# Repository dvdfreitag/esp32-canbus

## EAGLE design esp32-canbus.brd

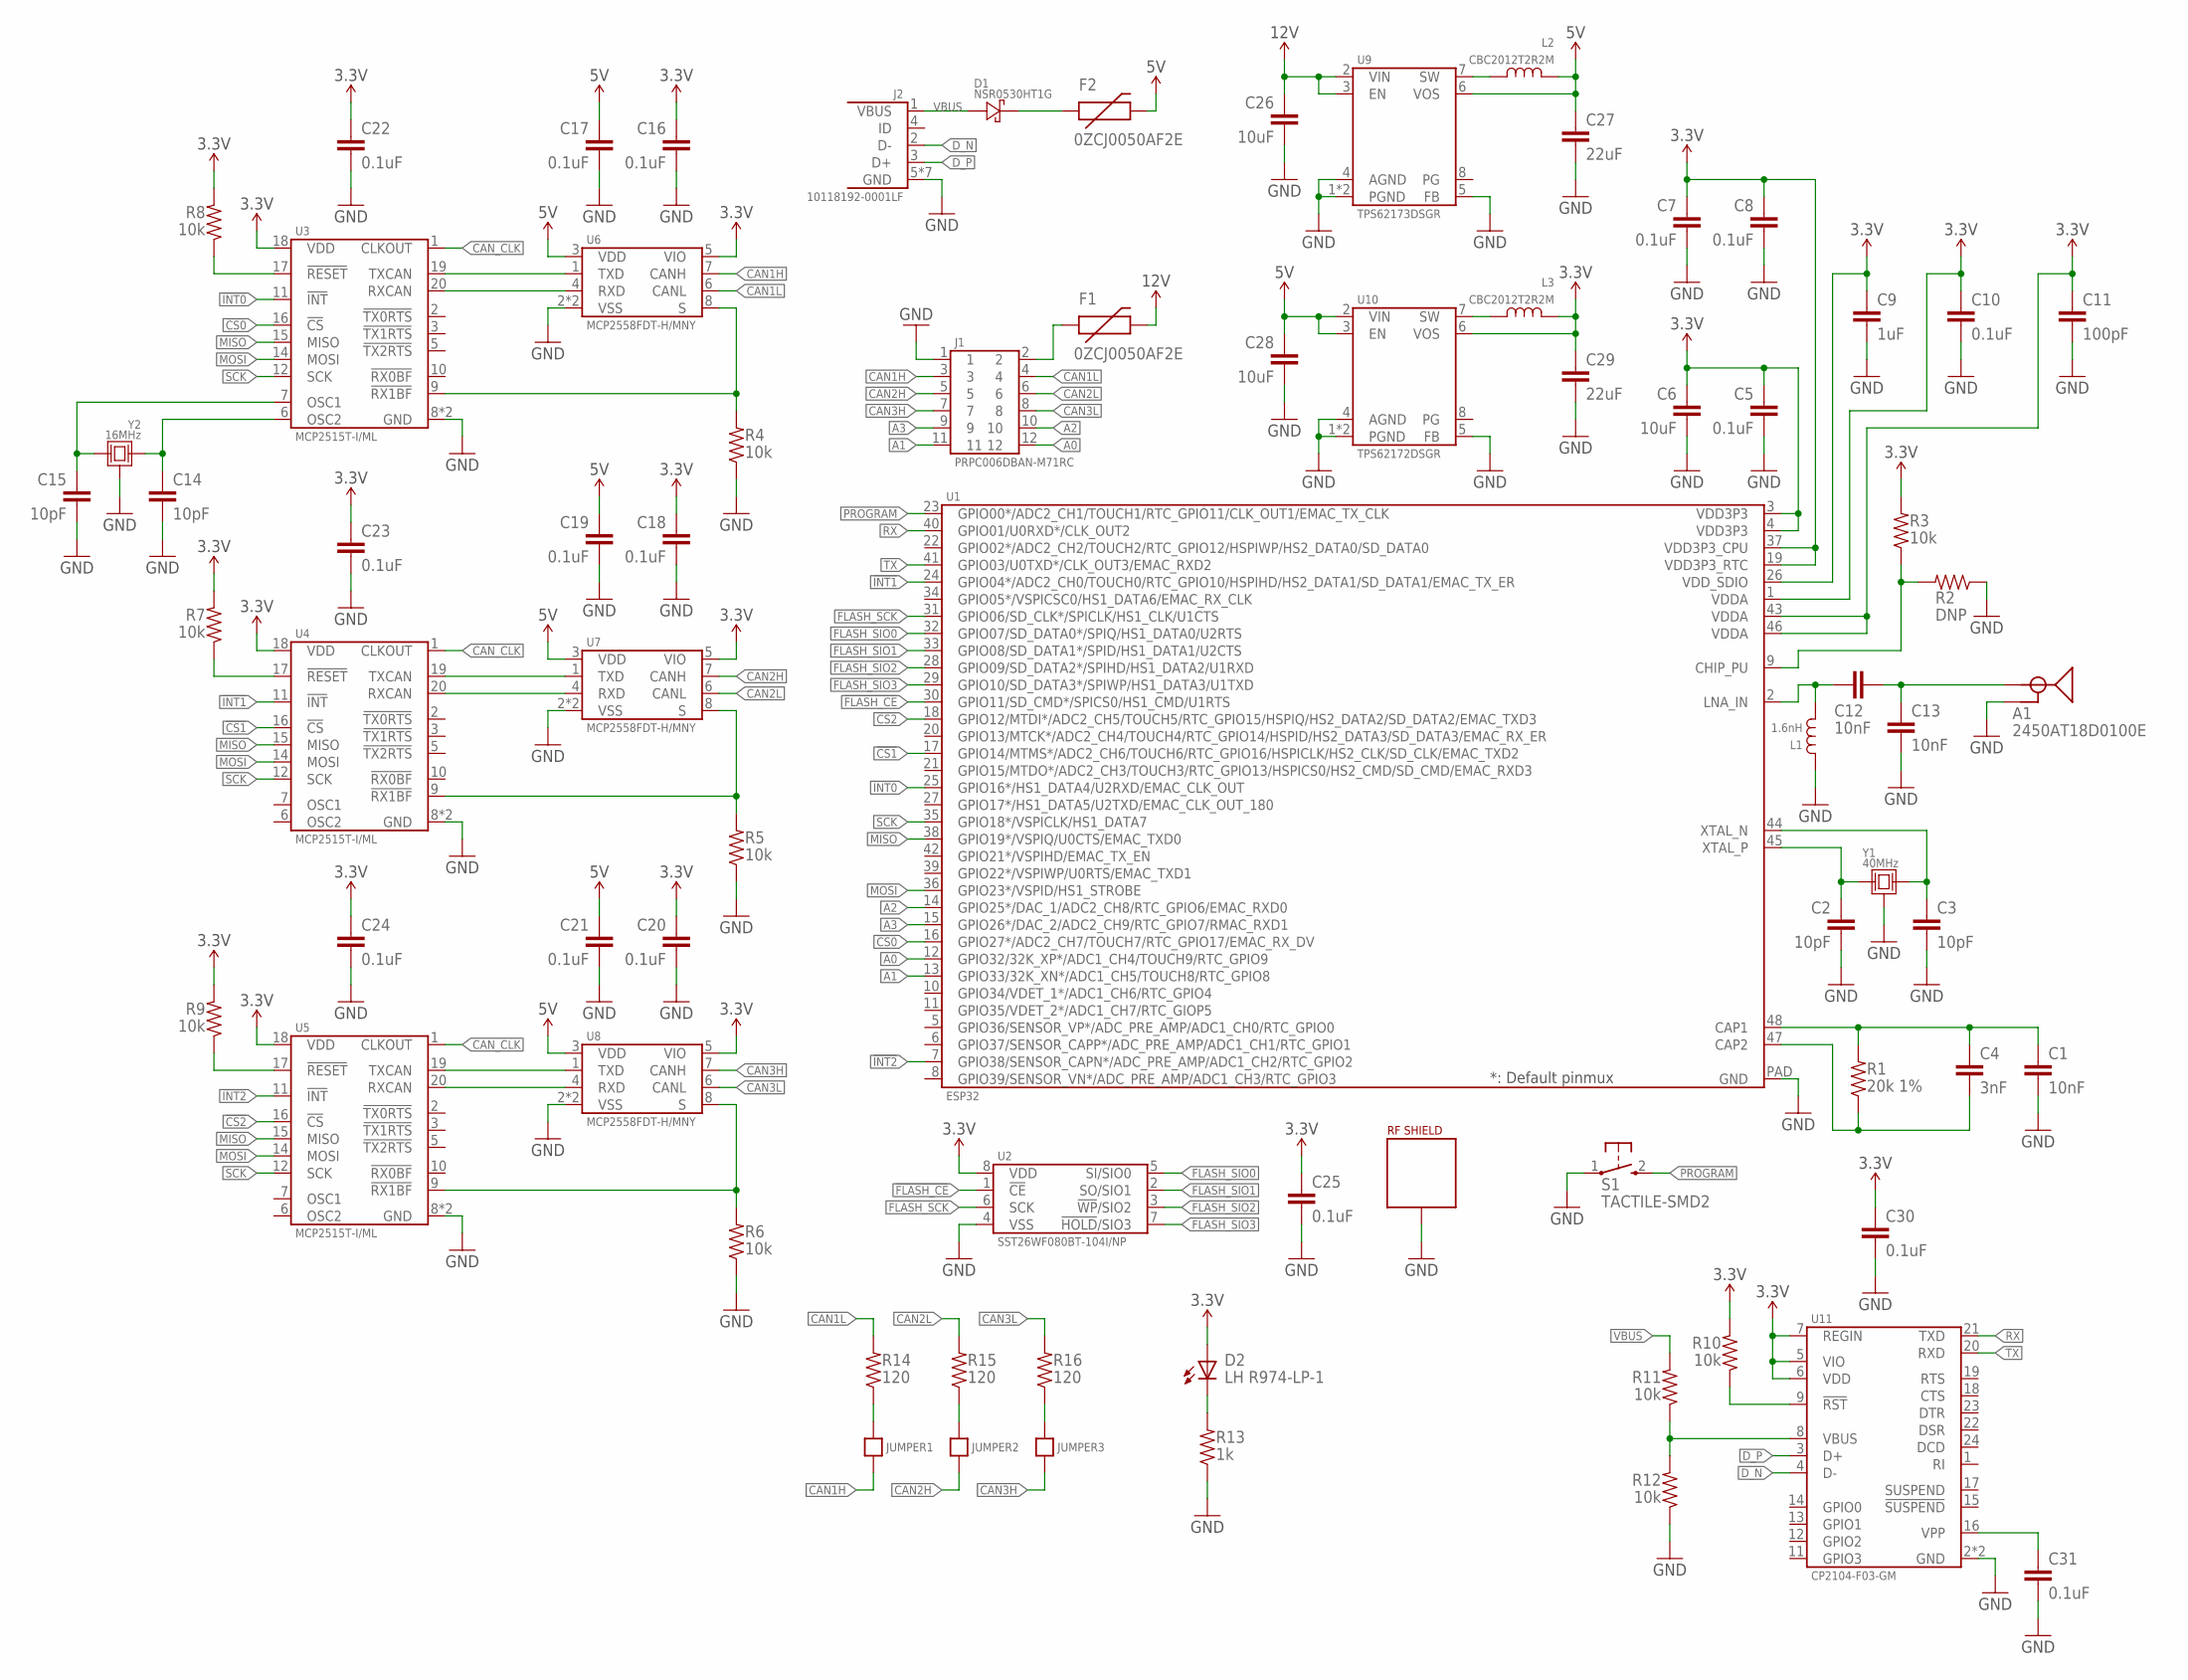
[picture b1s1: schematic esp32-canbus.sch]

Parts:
A1: 2450AT18D0100E; 4SMD-ANTENNA
C1, C12, C13: 10nF; 0603-CAP
C2, C3, C14, C15: 10pF; 0603-CAP
C4: 3nF; 0603-CAP
C5, C7, C8, C10, C16, C17, C18, C19, C20, C21, C22, C23, C24, C25, C30, C31: 0.1uF; 0603-CAP
C6, C26, C28: 10uF; 0603-CAP
C9: 1uF; 0603-CAP
C11: 100pF; 0603-CAP
C27, C29: 22uF; 0805-CAP
D1: NSR0530HT1G; SOD323
D2: LH R974-LP-1; 0805-LED
F1, F2: 0ZCJ0050AF2E; 1206-PTC
J1: PRPC006DBAN-M71RC; M06X2-PTH-H
J2: 10118192-0001LF
JUMPER1, JUMPER2, JUMPER3: JUMPER-NO
L1: 1.6nH; 0402-INDUCTOR
L2, L3: CBC2012T2R2M; 0805
R1: 20k 1%; 0603-CAP
R2: DNP; 0603-CAP
R3, R4, R5, R6, R7, R8, R9, R10, R11, R12: 10k; 0603-CAP
R13: 1k; 0603-CAP
R14, R15, R16: 120; 0603-CAP
S1: TACTILE-SMD2; PTS820-J15M-SMTR-LFS
SH1: BMI-S-102; RF_SHIELD-.65X.65
U1: ESP32
U2: SST26WF080BT-104I/NP; USON-8-2X3
U3, U4, U5: MCP2515T-I/ML; VQFN-20-4MM
U6, U7, U8: MCP2558FDT-H/MNY; TDFN-8-2X3
U9: TPS62173DSGR; DFN-8-2MM
U10: TPS62172DSGR; DFN-8-2MM
U11: CP2104-F03-GM; QFN-24-4X4
Y1: 40MHz; FA-238
Y2: 16MHz; FA-238

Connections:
3.3V: C5.1, C6.1, C7.1, C8.1, C9.1, C10.1, C11.1, C16.1, C18.1, C20.1, C22.1, C23.1, C24.1, C25.1, C29.1, C30.1, D2.A, L3.2, R3.2, R7.2, R8.2, R9.2, R10.2, U1.1 (VDDA), U1.3 (VDD3P3), U1.4 (VDD3P3), U1.19 (VDD3P3_RTC), U1.26 (VDD_SDIO), U1.37 (VDD3P3_CPU), U1.43 (VDDA), U1.46 (VDDA), U2.8 (VDD), U3.18 (VDD), U4.18 (VDD), U5.18 (VDD), U6.5 (VIO), U7.5 (VIO), U8.5 (VIO), U10.6 (VOS), U11.5 (VIO), U11.6 (VDD), U11.7 (REGIN)
5V: C17.1, C19.1, C21.1, C27.1, C28.1, F2.P$2 (2), L2.2, U6.3 (VDD), U7.3 (VDD), U8.3 (VDD), U9.6 (VOS), U10.2 (VIN), U10.3 (EN)
12V: C26.1, F1.P$2 (2), U9.2 (VIN), U9.3 (EN)
!CS0: U1.16 (GPIO27*/ADC2_CH7/TOUCH7/RTC_GPIO17/EMAC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), U3.16 (!CS)
!CS1: U1.17 (GPIO14/MTMS*/ADC2_CH6/TOUCH6/RTC_GPIO16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), U4.16 (!CS)
!CS2: U1.18 (GPIO12/MTDI*/ADC2_CH5/TOUCH5/RTC_GPIO15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), U5.16 (!CS)
!FLASH_CE: U1.30 (GPIO11/SD_CMD*/SPICS0/HS1_CMD/U1RTS), U2.1 (!CE)
!INT0: U1.25 (GPIO16*/HS1_DATA4/U2RXD/EMAC_CLK_OUT), U3.11 (!INT)
!INT1: U1.24 (GPIO04*/ADC2_CH0/TOUCH0/RTC_GPIO10/HSPI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), U4.11 (!INT)
!INT2: U1.7 (GPIO38/SENSOR_CAPN*/ADC_PRE_AMP/ADC1_CH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), U5.11 (!INT)
A0: J1.12, U1.12 (GPIO32/32K_XP*/ADC1_CH4/TOUCH9/RTC_GPIO9)
A1: J1.11, U1.13 (GPIO33/32K_XN*/ADC1_CH5/TOUCH8/RTC_GPIO8)
A2: J1.10, U1.14 (GPIO25*/DAC_1/ADC2_CH8/RTC_GPIO6/EMAC_R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)
A3: J1.9, U1.15 (GPIO26*/DAC_2/ADC2_CH9/RTC_GPIO7/RMAC_R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)
CAN1H: J1.3, JUMPER1.P$1, U6.7 (CANH)
CAN1L: J1.4, R14.2, U6.6 (CANL)
CAN2H: J1.5, JUMPER2.P$1, U7.7 (CANH)
CAN2L: J1.6, R15.2, U7.6 (CANL)
CAN3H: J1.7, JUMPER3.P$1, U8.7 (CANH)
CAN3L: J1.8, R16.2, U8.6 (CANL)
CAN_CLK: U3.1 (CLKOUT), U4.1 (CLKOUT), U5.1 (CLKOUT)
D_N: J2.2 (D-), U11.4 (D-)
D_P: J2.3 (D+), U11.3 (D+)
FLASH_SCK: U1.31 (GPIO06/SD_CLK*/SPICLK/HS1_CLK/U1CTS), U2.6 (SCK)
FLASH_SIO0: U1.32 (GPIO07/SD_DATA0*/SPIQ/HS1_DATA0/U2RTS), U2.5 (SI/SIO0)
FLASH_SIO1: U1.33 (GPIO08/SD_DATA1*/SPID/HS1_DATA1/U2CTS), U2.2 (SO/SIO1)
FLASH_SIO2: U1.28 (GPIO09/SD_DATA2*/SPIHD/HS1_DATA2/U1RXD), U2.3 (!WP!/SIO2)
FLASH_SIO3: U1.29 (GPIO10/SD_DATA3*/SPIWP/HS1_DATA3/U1TXD), U2.7 (!HOLD!/SIO3)
GND: A1.2 (GND), A1.3 (GND), A1.4 (GND), C1.2, C2.2, C3.2, C5.2, C6.2, C7.2, C8.2, C9.2, C10.2, C11.2, C13.2, C14.2, C15.2, C16.2, C17.2, C18.2, C19.2, C20.2, C21.2, C22.2, C23.2, C24.2, C25.2, C26.2, C27.2, C28.2, C29.2, C30.2, C31.2, J1.1, J2.5 (GND), J2.P$6 (GND), J2.P$7 (GND), J2.P$8 (GND), J2.P$9 (GND), J2.P$10 (GND), J2.P$11 (GND), L1.1, R2.1, R4.1, R5.1, R6.1, R12.1, R13.1, S1.1, SH1.P$1, SH1.P$2, SH1.P$3, SH1.P$4, SH1.P$5, SH1.P$6, SH1.P$7, SH1.P$8, SH1.P$9, SH1.P$10, SH1.P$11, SH1.P$12, U1.PAD (GND), U2.4 (VSS), U3.8 (GND), U3.PAD (GND), U4.8 (GND), U4.PAD (GND), U5.8 (GND), U5.PAD (GND), U6.2 (VSS), U6.PAD (VSS), U7.2 (VSS), U7.PAD (VSS), U8.2 (VSS), U8.PAD (VSS), U9.1 (PGND), U9.4 (AGND), U9.5 (FB), U9.PAD (PGND), U10.1 (PGND), U10.4 (AGND), U10.5 (FB), U10.PAD (PGND), U11.2 (GND), U11.PAD (GND), Y1.2 (GND), Y1.4 (GND), Y2.2 (GND), Y2.4 (GND)
MISO: U1.38 (GPIO19*/VSPIQ/U0CTS/EMAC_TXD0), U3.15 (MISO), U4.15 (MISO), U5.15 (MISO)
MOSI: U1.36 (GPIO23*/VSPID/HS1_STROBE), U3.14 (MOSI), U4.14 (MOSI), U5.14 (MOSI)
unnamed: C1.1, C4.1, R1.2, U1.48 (CAP1)
unnamed: C4.2, R1.1, U1.47 (CAP2)
unnamed: C3.1, U1.44 (XTAL_N), Y1.3 (2)
unnamed: C2.1, U1.45 (XTAL_P), Y1.1
unnamed: A1.1 (SIGNAL), C12.2, C13.1
unnamed: C12.1, L1.2, U1.2 (LNA_IN)
unnamed: R2.2, R3.1, U1.9 (CHIP_PU)
unnamed: U5.19 (TXCAN), U8.1 (TXD)
unnamed: U5.20 (RXCAN), U8.4 (RXD)
unnamed: R4.2, U3.9 (!RX1BF), U6.8 (S)
unnamed: U3.20 (RXCAN), U6.4 (RXD)
unnamed: U3.19 (TXCAN), U6.1 (TXD)
unnamed: R5.2, U4.9 (!RX1BF), U7.8 (S)
unnamed: U4.20 (RXCAN), U7.4 (RXD)
unnamed: U4.19 (TXCAN), U7.1 (TXD)
unnamed: R6.2, U5.9 (!RX1BF), U8.8 (S)
unnamed: C15.1, U3.7 (OSC1), Y2.3 (2)
unnamed: C14.1, U3.6 (OSC2), Y2.1
unnamed: R7.1, U4.17 (!RESET)
unnamed: R9.1, U5.17 (!RESET)
unnamed: R8.1, U3.17 (!RESET)
unnamed: R11.1, R12.2, U11.8 (VBUS)
unnamed: L2.1, U9.7 (SW)
unnamed: L3.1, U10.7 (SW)
unnamed: F1.P$1 (1), J1.2
unnamed: R10.1, U11.9 (!RST)
unnamed: D1.C, F2.P$1 (1)
unnamed: D2.C, R13.2
unnamed: JUMPER1.P$2, R14.1
unnamed: C31.1, U11.16 (VPP)
unnamed: JUMPER2.P$2, R15.1
unnamed: JUMPER3.P$2, R16.1
PROGRAM: S1.2 (3), U1.23 (GPIO00*/ADC2_CH1/TOUCH1/RTC_GPIO11/CLK_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)
RX: U1.40 (GPIO01/U0RXD*/CLK_OUT2), U11.21 (TXD)
SCK: U1.35 (GPIO18*/VSPICLK/HS1_DATA7), U3.12 (SCK), U4.12 (SCK), U5.12 (SCK)
TX: U1.41 (GPIO03/U0TXD*/CLK_OUT3/EMAC_RXD2), U11.20 (RXD)
VBUS: D1.A, J2.1 (VBUS), R11.2

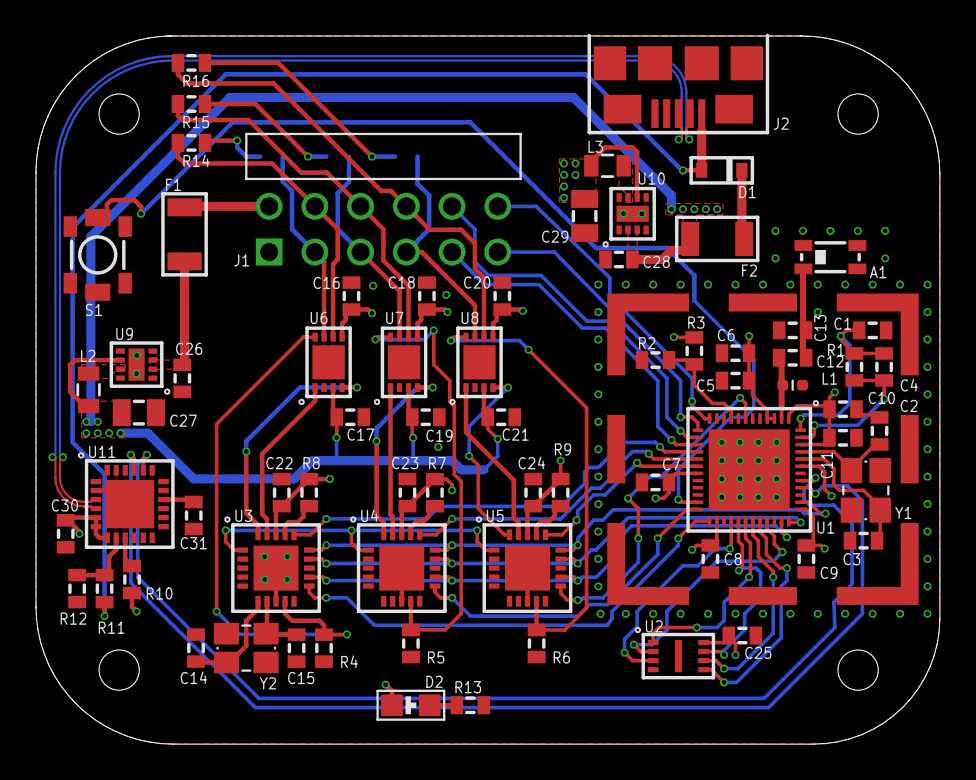
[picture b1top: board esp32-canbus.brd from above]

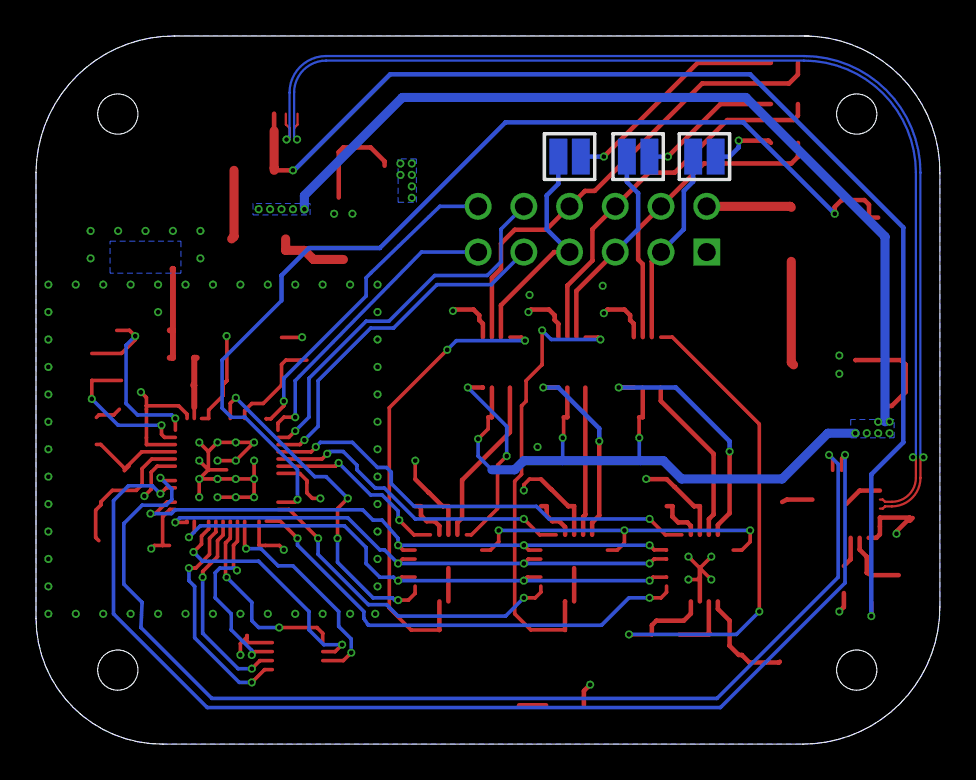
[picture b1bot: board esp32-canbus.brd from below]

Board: 4 copper layers, 50.2 x 39.3 mm, 75 parts (3 on the bottom side), 68 nets.

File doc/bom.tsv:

References	Qty	MPN	Description
A1	1	2450AT18D0100E	2.4GHz Chip antenna 1.5dBi
C1, C12, C13	3	CC0603KRX7R9BB103	Capacitor 10nF 0603 X7R
C2, C3, C14, C15	4	CC0603CRNPO9BN100	Capacitor 10pF 0603 C0G
C4	1	GRM1885C1H302JA01D	Capacitor 3nF 0603 C0G
C5, C7, C8, C10, C16, C17, C18, C19, C20, C21, C22, C23, C24, C25, C30, C31	16	CC0603KRX7R7BB104	Capacitor 0.1uF 0603 X7R
C6, C26, C28	3	GRM188R6YA106MA73D	Capacitor 10uF 0603 X5R
C9	1	CL10B105KP8NNNC	Capacitor 1uF 0603 X7R
C11	1	CC0603JRNPO9BN101	Capacitor 100pF 0603 C0G
C27, C29	2	CC0805MKX5R6BB226	Capacitor 22uF 0805 X5R
D1	1	NSR0530HT1G	Diode Schottky 30V 500mA
D2	1	LH R974-LP-1	Diode LED Red 0805
F1, F2	2	0ZCJ0050AF2E	Fuse PTC 500mA 1206
J1	1	PRPC006DBAN-M71RC	Connector 0.1" Horizontal 6x2
J2	1	10118192-0001LF	Connector USB Micro B
L1	1	MLG1005S1N6BTD25	Inductor 1.6nH 0402
L2, L3	2	CBC2012T2R2M	Inductor 2.2uH 0805 530mA
R1	1	RC0603FR-0720KL	Resistor 20k 1% 0603
R3, R4, R5, R6, R7, R8, R9, R10, R11, R12	10	RC0603FR-0710KL	Resistor 10k 1% 0603
R13	1	RC0603FR-071KL	Resistor 1k 1% 0603
R14, R15, R16	3	RC0603FR-07120RL	Resistor 120 1% 0603
S1	1	PTS820-J15M-SMTR-LFS	Switch Momentary SPST-NO
SH1	1	BMI-S-102	RF Shield 0.65"x0.65" 1 Piece
U1	1	ESP32	ESP32 WiFi/BLE SoC
U2	1	SST26WF080BT-104I/NP	NOR Flash 1MB USON-8 2mm x 3mm
U3, U4, U5	3	MCP2515T-I/ML	Controller CAN SPI VQFN-20 4mm x 4mm
U6, U7, U8	3	MCP2558FDT-H/MNY	TXRX CAN TDFN-8 2mm x 3mm
U9	1	TPS62173DSGR	Switching Regulator Fixed 5V 500mA WSON-8 2mm x 2mm
U10	1	TPS62172DSGR	Switching Regulator Fixed 3.3V 500mA WSON-8 2mm x 2mm
U11	1	CP2104-F03-GM	USB to UART Bridge w/ GPIO QFN-24 4mm x 4mm
Y2	1	403C11E16M00000	Crystal 16MHz ±10ppm 3.2mm x 2.5mm
Y1	1	403C11A40M00000	Crystal 40MHz ±10ppm 3.2mm x 2.5mm

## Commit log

2016-09-07 Create LICENSE
2016-09-08 Update board
    Rout mode of the board and a few edits in the schematic
2016-09-09 Update board
    Finish board layou, tweak a few things in schematic, and add documents
    (ger ber files, pdf schematic)
